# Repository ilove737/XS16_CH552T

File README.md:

# XS16_CH552T

## 介绍
基于CH552T微控制器实现的XS16键盘固件项目（16键，4×4 矩阵）。这是一个USB键盘/鼠标复合设备固件，使用CH552系列微控制器实现键盘和鼠标功能。

## 项目特点
- 支持USB键盘和鼠标功能（复合设备）
- 基于CH552T微控制器
- 支持键盘扫描矩阵（4行×4列，共16键）
- 包含定时器和GPIO控制功能
- 支持数据闪存存储

## 硬件平台
- 微控制器：CH552T
- 开发板：XS16

## 编译环境设置

### Linux编译环境
本项目已经配置为可以在Linux环境下使用SDCC编译器编译：

1. 安装SDCC编译器：
   ```bash
   make install-deps
   ```

2. 编译项目：
   ```bash
   make clean
   make all
   ```

3. 编译输出：
   - 生成的文件将存放在 `build/` 目录中
   - 链接中间产物：`build/XS16_CH552T.ihx`（SDCC 链接输出）
   - 最终固件：`build/XS16_CH552T.hex`（由 `.ihx` 经 `packihx` 转换，可烧录）

## 项目结构
- `src/main.c` - 主程序入口
- `src/CompositeKM.C/CompositeKM.H` - USB键盘鼠标复合设备实现
- `src/CH552.H` - SDCC兼容的CH552头文件
- `src/Debug.C/Debug.H` - 调试和延时函数
- `src/Timer.C/Timer.H` - 定时器功能
- `src/GPIO.C/GPIO.H` - GPIO控制功能
- `src/UART1.C/UART1.H` - UART1 串口功能
- `src/scanKey.c/scanKey.h` - 键盘扫描功能
- `src/DataFlash.C/DataFlash.H` - 数据闪存功能
- `src/FlashWrite.c/FlashWrite.h` - Flash 写入功能
- `src/keyMap.h` - 键位映射定义
- `Makefile` - Linux编译脚本

## 编译说明
- 使用SDCC (Small Device C Compiler) 进行编译
- 目标微控制器：CH552T
- 可用代码区：约 14KB（Makefile 中 `--code-size 0x3800`，CH552 的 16KB Flash 需给 Bootloader 留出空间）
- 已配置为支持USB设备模式

## 输出文件
- `XS16_CH552T.hex` - 可烧录的Intel HEX格式固件
- `XS16_CH552T.ihx` - Intel HEX格式中间文件
- 各种调试文件（.asm, .lst, .map等）在 build 目录中

## 烧录方式
生成的hex文件可以通过支持CH552的编程器进行烧录，例如：
- 使用本项目自带命令（需先安装 `wchisp`）：
  ```bash
  make flash          # 等价于 wchisp flash build/XS16_CH552T.hex
  ```
  其中 `wchisp` 可通过 `cargo install wchisp` 或各平台包管理器安装。
- ISP编程器
- 相关的CH55x专用烧录工具

## 注意事项
- 项目已适配SDCC编译器，不再依赖Keil C51
- 所有CH552特定寄存器定义已转换为SDCC兼容格式
- USB功能已适配CH552 USB控制器

## 配套工具

本项目除了固件，还提供了两个键位编辑器，用于图形化编辑固件的键位映射、场景配置，并通过 USB / WebHID 与设备通信。

### 桌面端编辑器（tools/app，Tauri v2）

基于 Tauri v2 的跨平台桌面应用（前端为无框架 Vanilla JS，后端为 Rust）。

- 提供图形化键位编辑、设备读写（HID 通信）。
- 场景名支持从当前打开的应用列表中选取（下拉选择框，窗口聚焦时自动刷新）。
- Linux 下连接键盘权限不足时，可自动安装 udev 规则（需输入管理员密码）。
- 支持「按激活应用自动切换场景」功能（见下节）。
- 构建方式：
  ```bash
  # Linux 下需先安装系统依赖
  sudo apt-get install -y libdbus-1-dev libudev-dev libgtk-3-dev \
    libwebkit2gtk-4.1-dev libjavascriptcoregtk-4.1-dev libsoup-3.0-dev

  cd tools/app && npm install   # 安装前端依赖
  npm run build                 # 打包前端到 dist/
  make -C tools/app app         # 构建发布包
  # 或 npm run tauri-dev 进行开发调试
  ```

### Web 端编辑器（tools/web，WebHID）

基于浏览器 WebHID 的纯前端编辑器，无需安装，适合快速修改键位。

- 受浏览器沙箱限制，无法读取前台窗口，因此**不支持**「自动匹配激活应用」功能。
- 启动方式：
  ```bash
  cd tools/web && python3 -m http.server 8000
  # 浏览器打开 http://localhost:8000 （WebHID 需 localhost 或 HTTPS）
  ```

## 自动匹配激活应用（场景自动切换）

编辑器在后台轮询当前前台（激活）窗口的应用名，与固件中配置的场景槽应用名匹配，命中即自动下发对应场景，未命中则切回主层（generic）。

- 实现位置：Rust 后端 `tools/app/src-tauri/src/lib.rs`
  （`active_app_impl` 取前台应用 + `match_app_to_scene` 匹配 + `poll_loop` 轮询下发）。
- **平台支持：**
  - ✅ **Linux**：通过 X11 协议（`x11rb` / `libxcb`）读取前台窗口，功能完整可用。
  - ⚠️ **macOS / Windows**：**暂不支持**。前台窗口探测依赖各平台原生窗口系统接口
    （macOS 的 `NSWorkspace`、Windows 的 `GetForegroundWindow` 等），
    当前版本仅在 Linux 上实现，路线图见下方 TODO。

## 待办 / 路线图

### 在 macOS / Windows 实现「自动匹配激活应用」功能（方案 A：原生 FFI）

> 目标：用 Rust 直接调用各平台原生窗口接口，替代当前仅 Linux 可用的 X11 实现，
> 使桌面端编辑器的「自动切换场景」功能在三个平台上都可用。

1. **[Cargo.toml]** 新增平台专属依赖：
   - macOS：`objc` / `cocoa`（调用 `NSWorkspace.frontmostApplication` 取 `bundleIdentifier` / `localizedName`）
   - Windows：`windows` 或 `winapi`（调用 `GetForegroundWindow` / `GetWindowThreadProcessId` / `QueryFullProcessImageName`）
2. **[lib.rs]** 把 `active_app_impl` 由「仅 Linux」改为三平台各自实现：
   - Linux：现有 X11 实现（保持不变）
   - macOS：Objective-C FFI 取前台应用标识
   - Windows：Win32 API 取前台窗口进程路径，解析出 exe 名
3. **[lib.rs]** `match_app_to_scene` / `send_scene_impl` / `poll_loop` 架构完全复用，
   仅「取前台应用名」一步做成平台可插拔（共用同一套匹配/下发逻辑）。
4. **[lib.rs]** 去掉 `active_app` / `get_poll_status` / `start_auto_poll` / `stop_auto_poll`
   中 `#[cfg(not(target_os = "linux"))]` 的 Err stub，改为各平台真实实现
   （或至少 macOS/Windows 各自实现，最后兜底返回 `Err`）。
5. **[CI]** 调整 `.github/workflows/build.yml`，确保 macOS / Windows target
   链接对应平台 SDK 成功（注意 Windows 的 MSVC vs gnu target 差异）。
6. **[前端 tools/app/src/app.js]** 把"自动匹配仅 Linux"的提示文案更新为按平台动态提示。

## 许可证
本项目固件基于 WCH（CH552）官方示例代码改编开发，遵循原示例代码所附许可；新增与修改部分目前**未声明明确许可证**，如需用于分发或二次开发请先联系作者确认。

> 说明：随 Tauri 依赖引入的第三方库（如 `tools/app/src-tauri/target/` 下）分别遵循其各自的许可证（如 Apache-2.0、MIT 等），与本仓库固件代码许可无关。

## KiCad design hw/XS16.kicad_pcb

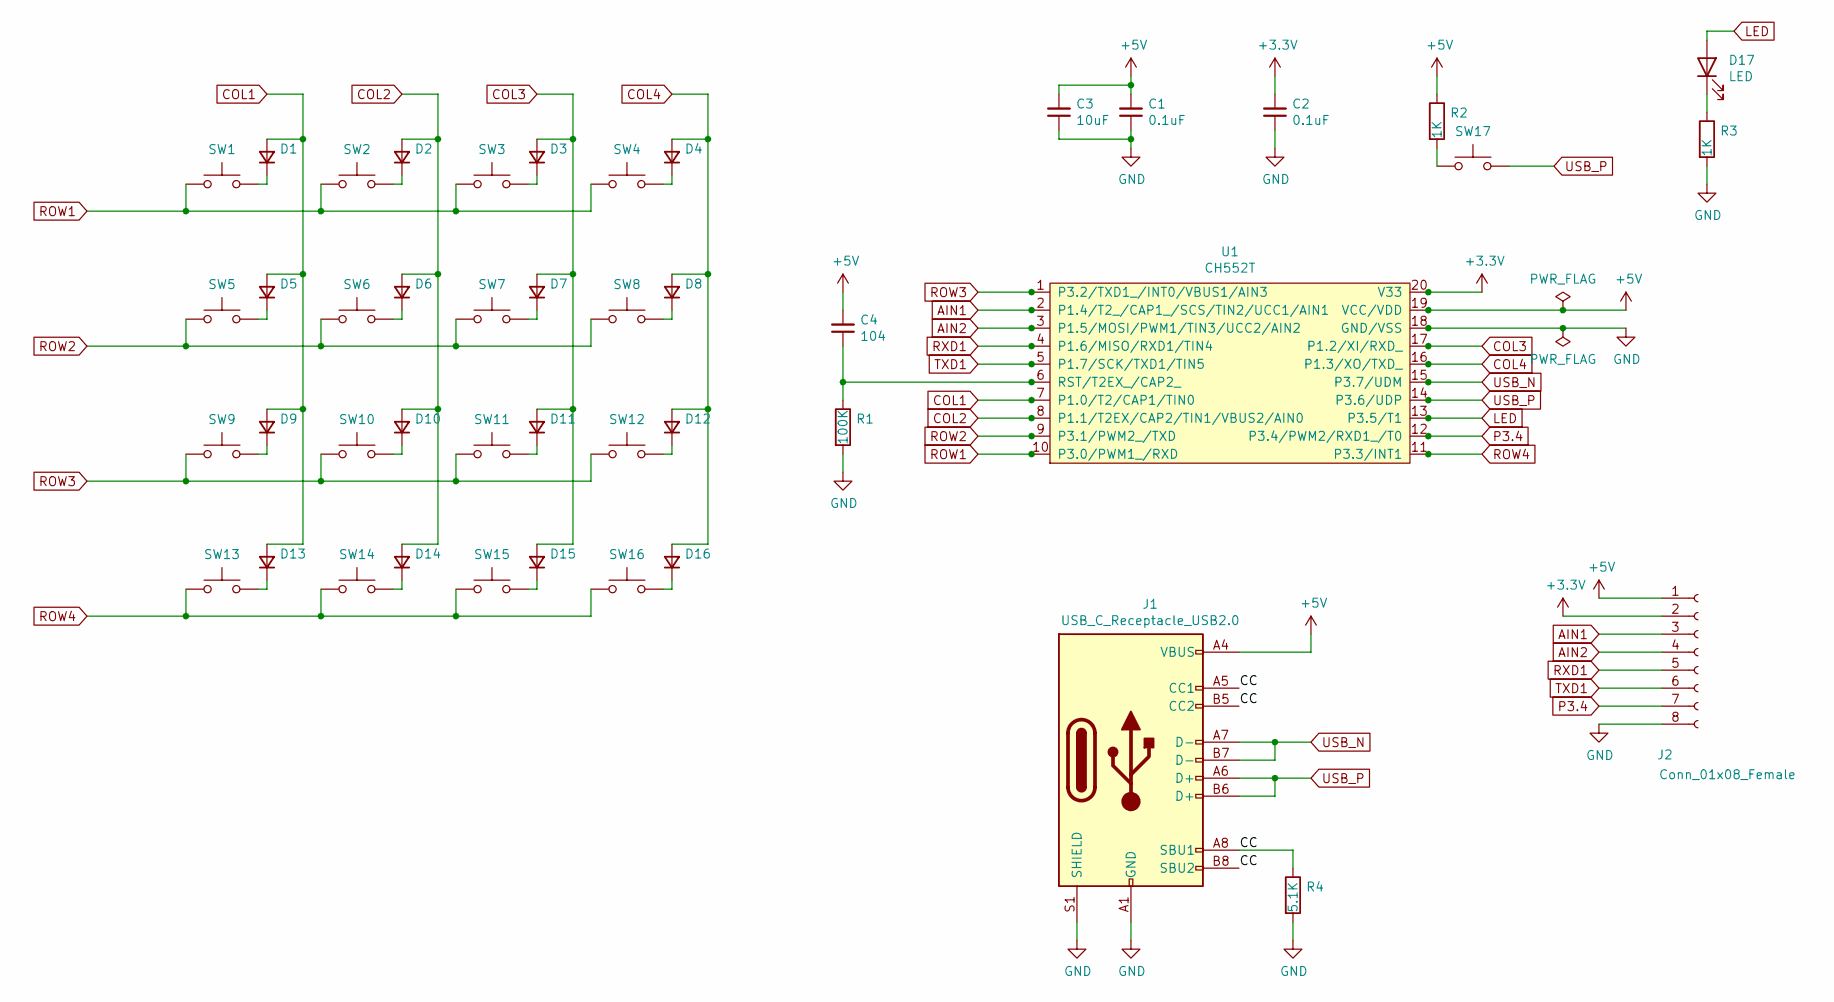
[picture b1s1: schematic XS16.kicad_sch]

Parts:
C1, C2: 0.1uF; C_0603_1608Metric
C3: 10uF; C_0603_1608Metric
C4: 104; C_0603_1608Metric
D1, D2, D3, D4, D5, D6, D7, D8, D9, D10, D11, D12, D13, D14, D15, D16: 1N4148; D_SOD-323
D17: LED; LED_0603_1608Metric
J1: USB_C_Receptacle_USB2.0; USB_C_Receptacle_Palconn_UTC16-G
J2: Conn_01x08_Female; PinHeader_1x08_P2.54mm_Vertical
R1: 100K; R_0603_1608Metric
R2, R3: 1K; R_0603_1608Metric
R4: 5.1K; R_0603_1608Metric
SW1, SW2, SW3, SW4, SW5, SW6, SW7, SW8, SW9, SW10, SW11, SW12, SW13, SW14, SW15, SW16: SW_Push; SW_Cherry_MX1A_1.00u_PCB_lxs
SW17: SW_Push; SW_Push_1P1T_NO_CK_KMR2
U1: CH552T; TSSOP-20_4.4x6.5mm_P0.65mm

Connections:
+3V3: C2.2, J2.2, U1.20 (V33)
+5V: C1.2, C3.2, C4.2, J1.A4 (VBUS), J1.A9 (VBUS), J1.B4 (VBUS), J1.B9 (VBUS), J2.1, R2.1, U1.19 (VCC/VDD)
/CC: J1.A5 (CC1), J1.A8 (SBU1), J1.B5 (CC2), J1.B8 (SBU2), R4.1
AIN1: J2.3, U1.2 (P1.4/T2_/CAP1_/SCS/TIN2/UCC1/AIN1)
AIN2: J2.4, U1.3 (P1.5/MOSI/PWM1/TIN3/UCC2/AIN2)
COL1: D1.2 (A), D5.2 (A), D9.2 (A), D13.2 (A), U1.7 (P1.0/T2/CAP1/TIN0)
COL2: D2.2 (A), D6.2 (A), D10.2 (A), D14.2 (A), U1.8 (P1.1/T2EX/CAP2/TIN1/VBUS2/AIN0)
COL3: D3.2 (A), D7.2 (A), D11.2 (A), D15.2 (A), U1.17 (P1.2/XI/RXD_)
COL4: D4.2 (A), D8.2 (A), D12.2 (A), D16.2 (A), U1.16 (P1.3/XO/TXD_)
GND: C1.1, C2.1, C3.1, J1.A1 (GND), J1.A12 (GND), J1.B1 (GND), J1.B12 (GND), J1.S1 (SHIELD), J1.SH, J2.8, R1.2, R3.2, R4.2, U1.18 (GND/VSS)
LED: D17.2 (A), U1.13 (P3.5/T1)
unnamed: C4.1, R1.1, U1.6 (RST/T2EX_/CAP2_)
unnamed: D1.1 (K), SW1.2
unnamed: D2.1 (K), SW2.2
unnamed: D3.1 (K), SW3.2
unnamed: D4.1 (K), SW4.2
unnamed: D5.1 (K), SW5.2
unnamed: D6.1 (K), SW6.2
unnamed: D7.1 (K), SW7.2
unnamed: D8.1 (K), SW8.2
unnamed: D9.1 (K), SW9.2
unnamed: D10.1 (K), SW10.2
unnamed: D11.1 (K), SW11.2
unnamed: D12.1 (K), SW12.2
unnamed: D13.1 (K), SW13.2
unnamed: D14.1 (K), SW14.2
unnamed: D15.1 (K), SW15.2
unnamed: D16.1 (K), SW16.2
unnamed: D17.1 (K), R3.1
unnamed: R2.2, SW17.1
P3.4: J2.7, U1.12 (P3.4/PWM2/RXD1_/T0)
ROW1: SW1.1, SW2.1, SW3.1, SW4.1, U1.10 (P3.0/PWM1_/RXD)
ROW2: SW5.1, SW6.1, SW7.1, SW8.1, U1.9 (P3.1/PWM2_/TXD)
ROW3: SW9.1, SW10.1, SW11.1, SW12.1, U1.1 (P3.2/TXD1_/INT0/VBUS1/AIN3)
ROW4: SW13.1, SW14.1, SW15.1, SW16.1, U1.11 (P3.3/INT1)
RXD1: J2.5, U1.4 (P1.6/MISO/RXD1/TIN4)
TXD1: J2.6, U1.5 (P1.7/SCK/TXD1/TIN5)
USB_N: J1.A7 (D-), J1.B7 (D-), U1.15 (P3.7/UDM)
USB_P: J1.A6 (D+), J1.B6 (D+), SW17.2, U1.14 (P3.6/UDP)

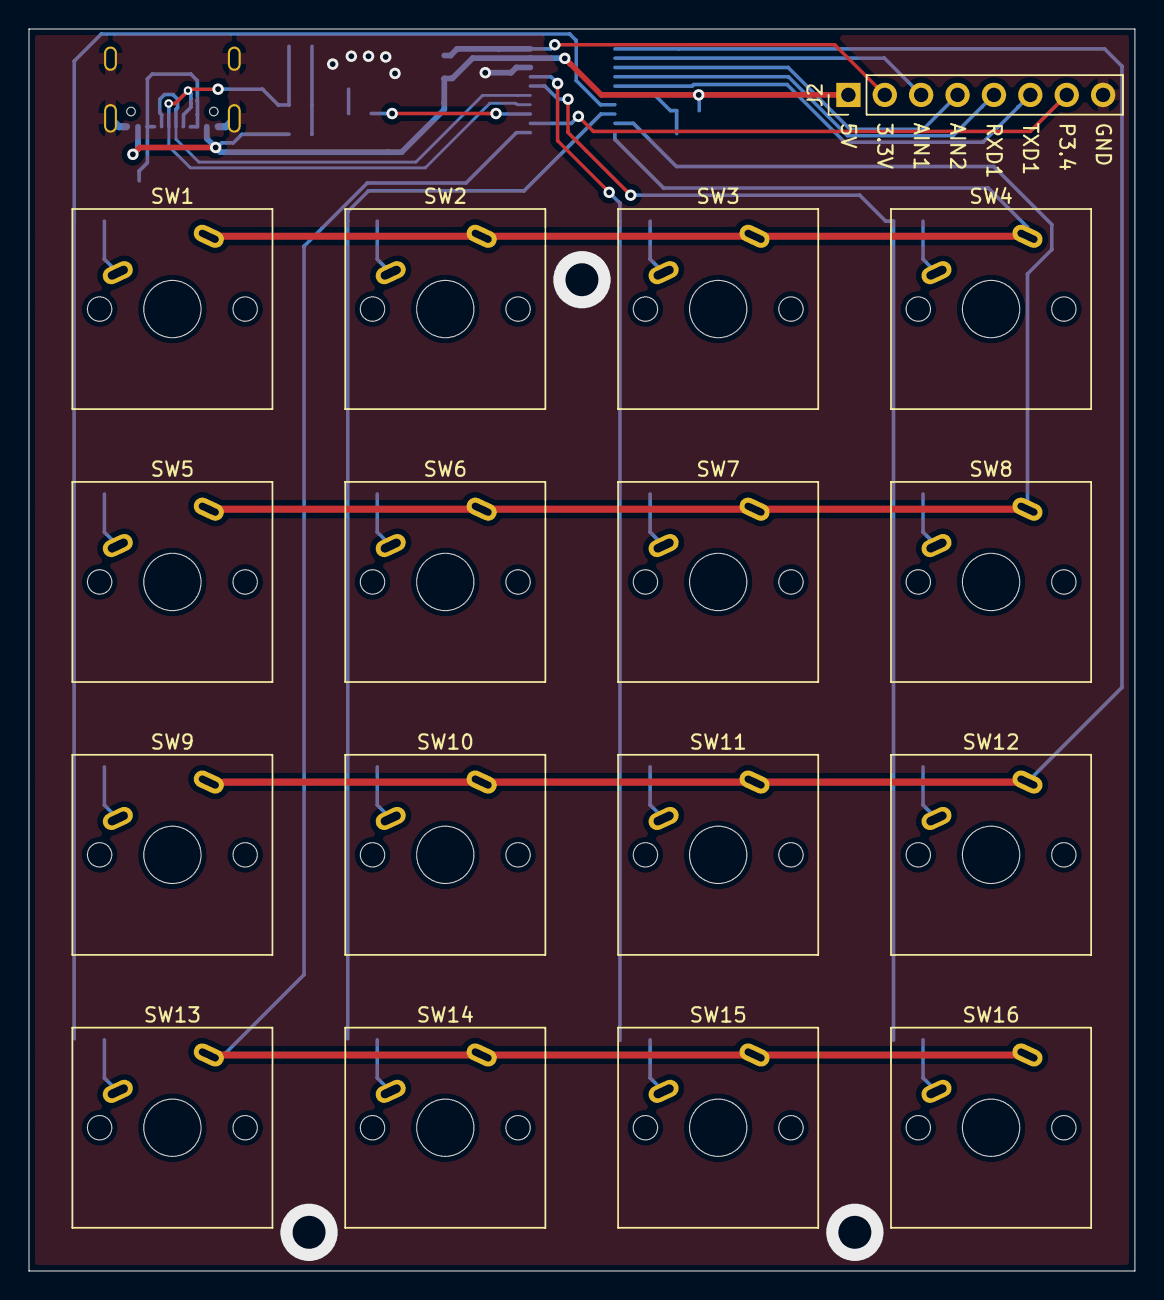
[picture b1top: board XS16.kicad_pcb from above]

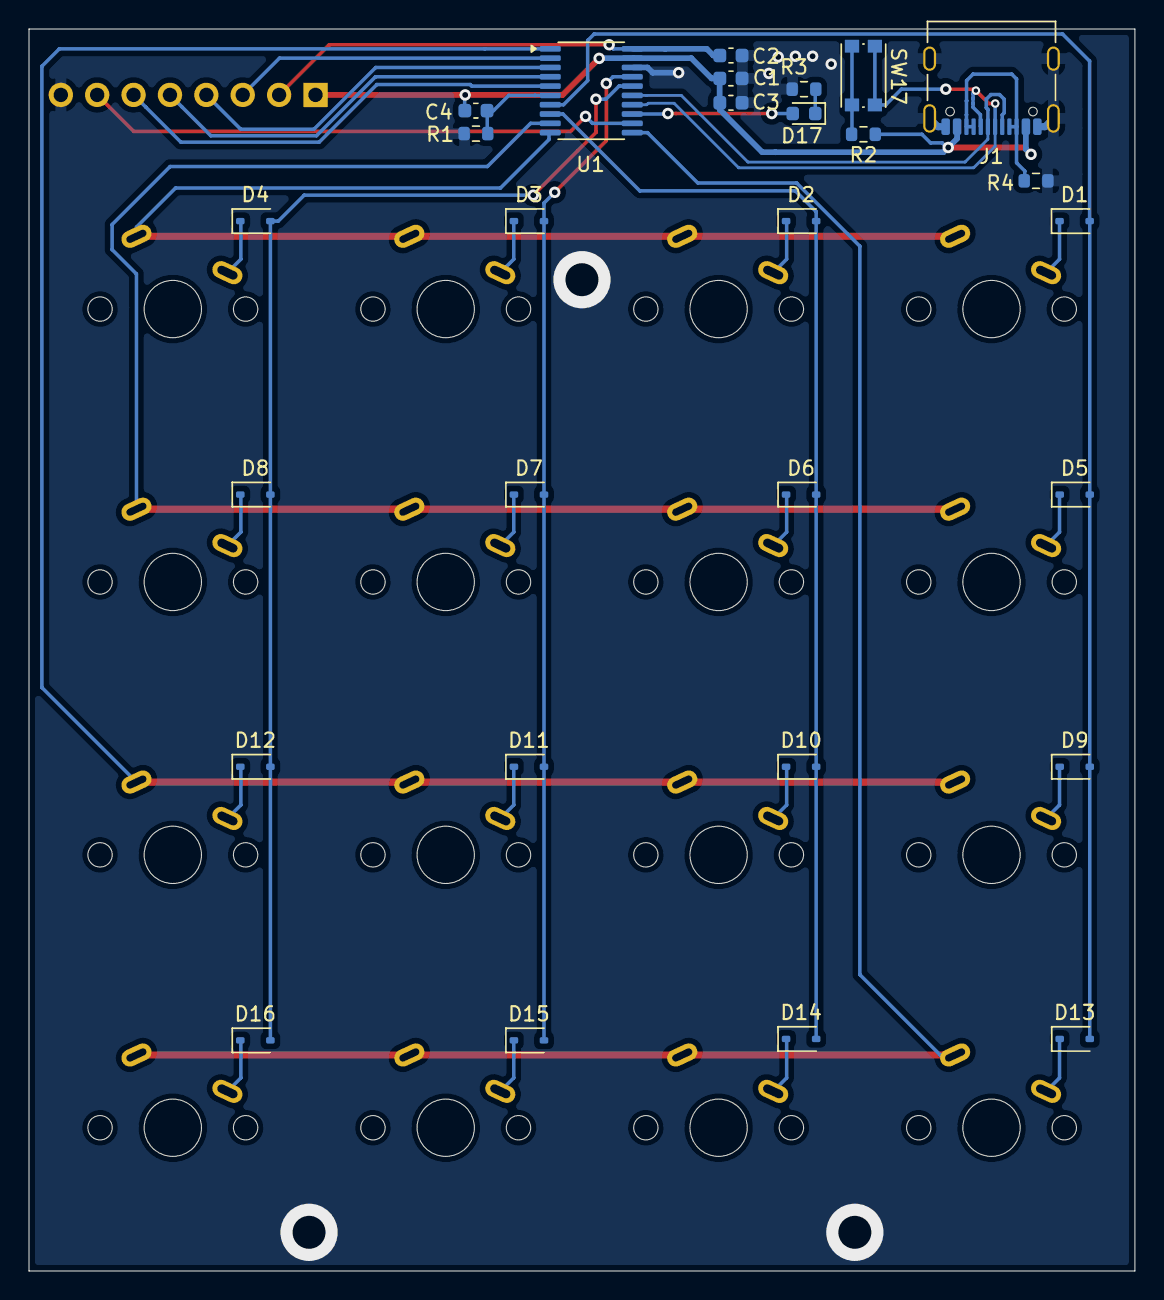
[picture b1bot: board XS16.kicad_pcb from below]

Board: 2 copper layers, 77.2 x 86.7 mm, 45 parts (28 on the bottom side), 39 nets.
